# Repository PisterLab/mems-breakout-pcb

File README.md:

# MEMS Breakout PCBs

This repo contains KiCad projects for PCBs designed to break out MEMS devices for research/development.

## MEMS Breakout W50

This PCB is contained in the `mems_breakout_w50/` directory and provides 50 connections from wire bond pads on the MEMS die that are routed to standard pitch (2.54mm) headers. 

Gerbers & drill files are provided for manufacturing at `mems_breakout_w50/memsbreakout_w5-v0_gerbers_drill_files.zip`

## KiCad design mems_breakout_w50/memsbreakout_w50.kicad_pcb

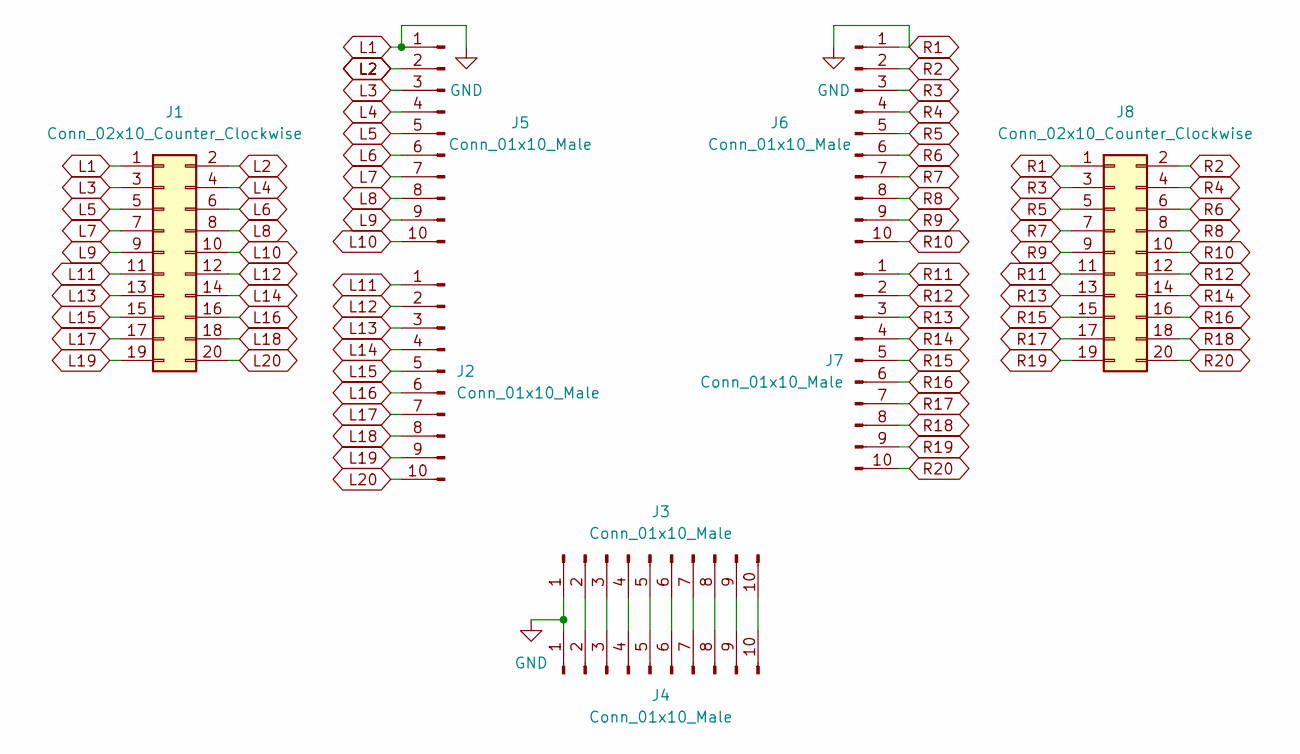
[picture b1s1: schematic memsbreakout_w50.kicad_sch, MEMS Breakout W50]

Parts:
J1, J8: Conn_02x10_Counter_Clockwise; PinHeader_2x10_P2.54mm_Vertical
J2, J3, J5, J6, J7: Conn_01x10_Male; wirebondarray-dteal
J4: Conn_01x10_Male; PinHeader_1x10_P2.54mm_Vertical

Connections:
L2: J1.2, J5.2
L3: J1.3, J5.3
L4: J1.4, J5.4
L5: J1.5, J5.5
L6: J1.6, J5.6
L7: J1.7, J5.7
L8: J1.8, J5.8
L9: J1.9, J5.9
L10: J1.10, J5.10
L11: J1.11, J2.1
L12: J1.12, J2.2
L13: J1.13, J2.3
L14: J1.14, J2.4
L15: J1.15, J2.5
L16: J1.16, J2.6
L17: J1.17, J2.7
L18: J1.18, J2.8
L19: J1.19, J2.9
L20: J1.20, J2.10
unnamed: J3.2, J4.2
unnamed: J3.3, J4.3
unnamed: J3.4, J4.4
unnamed: J3.5, J4.5
unnamed: J3.6, J4.6
unnamed: J3.7, J4.7
unnamed: J3.8, J4.8
unnamed: J3.9, J4.9
unnamed: J3.10, J4.10
R2: J6.2, J8.2
R3: J6.3, J8.3
R4: J6.4, J8.4
R5: J6.5, J8.5
R6: J6.6, J8.6
R7: J6.7, J8.7
R8: J6.8, J8.8
R9: J6.9, J8.9
R10: J6.10, J8.10
R11: J7.1, J8.11
R12: J7.2, J8.12
R13: J7.3, J8.13
R14: J7.4, J8.14
R15: J7.5, J8.15
R16: J7.6, J8.16
R17: J7.7, J8.17
R18: J7.8, J8.18
R19: J7.9, J8.19
R20: J7.10, J8.20

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
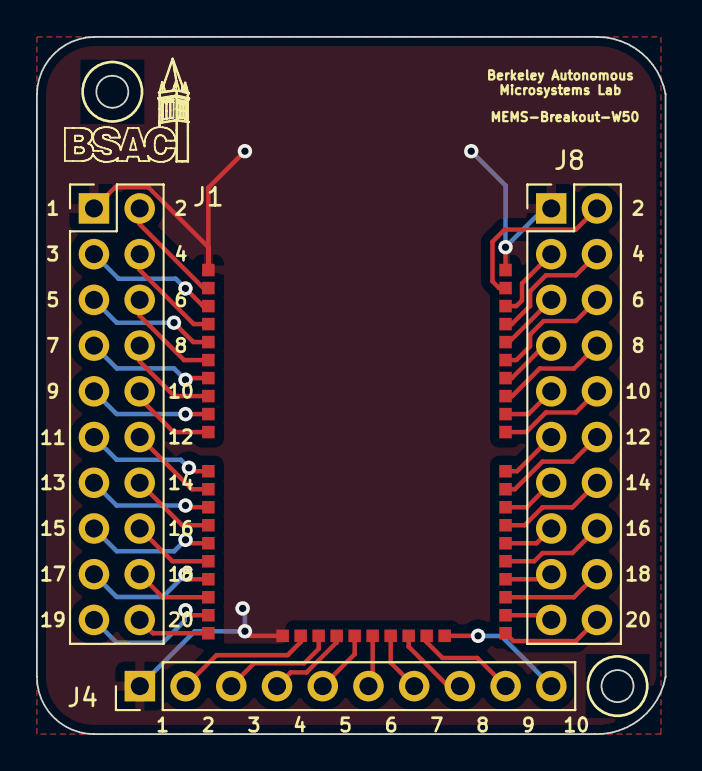
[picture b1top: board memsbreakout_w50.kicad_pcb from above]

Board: 2 copper layers, 34.9 x 38.7 mm, 8 parts (0 on the bottom side), 48 nets.
